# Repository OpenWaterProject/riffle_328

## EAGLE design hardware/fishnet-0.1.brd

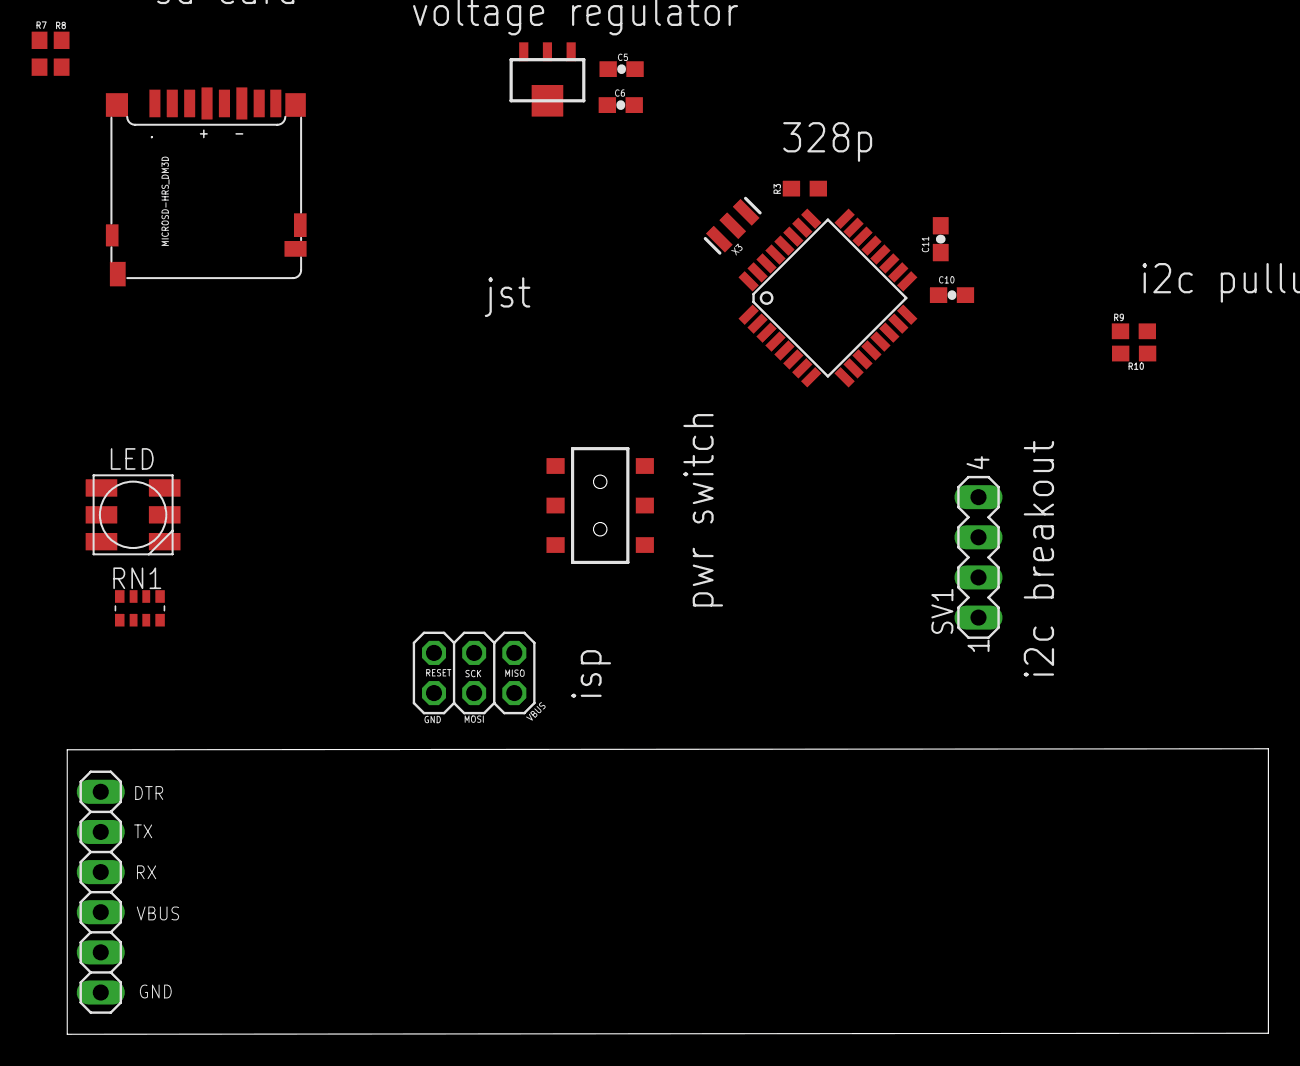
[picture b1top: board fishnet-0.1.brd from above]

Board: 2 copper layers, 76.0 x 18.1 mm, 20 parts (1 on the bottom side), 25 nets, no tracks yet.

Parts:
C5, C6: 10uF; 0603-CAP
C10, C11: 0.1uF; 0603-CAP
CN1: JST-PH-2-SMT-RA
IC1: ATMEGA328P; TQFP32-08
IC4: MCP1700-33; SOT89
ISP: 2X03
J1: AYZ0202
JP2: 1X06
LED: RGBLED5050
R3, R9, R10: 10K; 0603-NO
R7, R8: 50K; 0603-NO
RN1: EXB38V
SV1: MA04-1
U$1: MICROSD-HRS_DM3D; DM3D
X3: 16 MHz; RESONATOR-SMD

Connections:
AREF: C10.1, IC1.20
D4: IC1.2, RN1.4
D5: IC1.9, RN1.2
D6: IC1.10, RN1.3
D7: IC1.11, U$1.CD/DAT3
GND: C5.2, C6.2, C10.2, C11.1, CN1.2, IC1.3, IC1.5, IC1.21, IC4.1, ISP.6, JP2.1, LED.4, LED.5, LED.6, SV1.2, U$1.GND1, U$1.GND2, U$1.GND3, U$1.GND4, U$1.SW_A, U$1.SW_B, U$1.VSS, X3.2
MISO: IC1.16, ISP.1, U$1.DAT0
MOSI: IC1.15, ISP.4, U$1.CMD
unnamed: LED.3, RN1.5
unnamed: IC1.7, X3.1
unnamed: IC1.8, X3.3
unnamed: LED.1, RN1.7
unnamed: LED.2, RN1.6
unnamed: R7.2, U$1.DAT1
unnamed: R8.1, U$1.DAT2
RESET: IC1.29, ISP.5, R3.1
RXD: IC1.30, JP2.4
SCK: IC1.17, ISP.3, U$1.CLK
SCL: IC1.28, R9.1, SV1.3
SDA: IC1.27, R10.1, SV1.4
TXD: IC1.31, JP2.5
VBAT: CN1.1, J1.2
VBUS: ISP.2, JP2.3
VCC: C6.1, C11.2, IC1.4, IC1.6, IC1.18, IC4.3, R3.2, R7.1, R8.2, R9.2, R10.2, SV1.1, U$1.VDD
VDD: C5.1, IC4.2, J1.1

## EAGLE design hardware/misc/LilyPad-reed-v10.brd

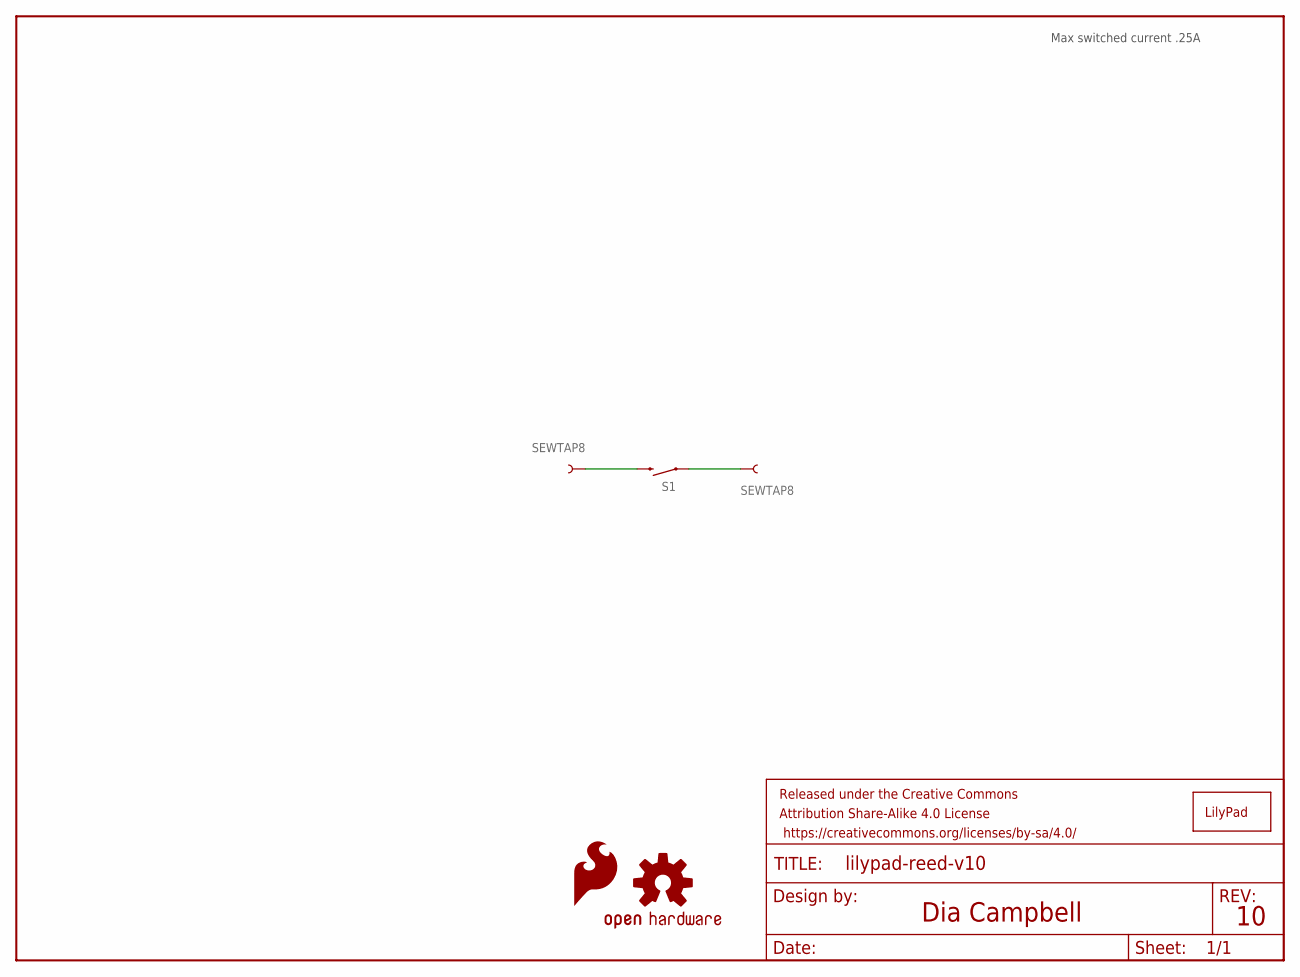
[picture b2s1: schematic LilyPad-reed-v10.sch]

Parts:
FRAME1: FRAME-LETTER; CREATIVE_COMMONS
LOGO1: OSHW-LOGOS-COPPER; OSHW-LOGO-S_COPPER
LOGO2: SFE_LOGO_FLAME.1COP; SFE_LOGO_FLAME_COPPER_.1
S1: REED; REED_SWITCH_PLASTIC
SLIDEOFF: SEWTAP8; PETAL-MEDIUM-2SIDE
SLIDEON: SEWTAP8; PETAL-MEDIUM-2SIDE
U$1: LOGO-LPLP; LOGO-LILYPAD

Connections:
unnamed: S1.P$2 (2), SLIDEOFF.1
unnamed: S1.P$1 (1), SLIDEON.1

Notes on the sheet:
Dia Campbell
Max switched current .25A

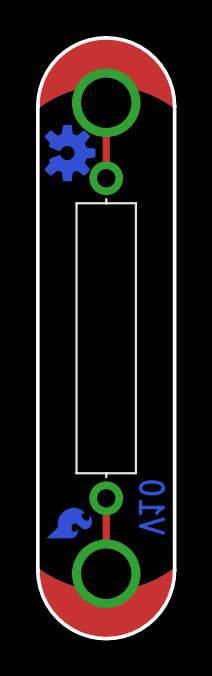
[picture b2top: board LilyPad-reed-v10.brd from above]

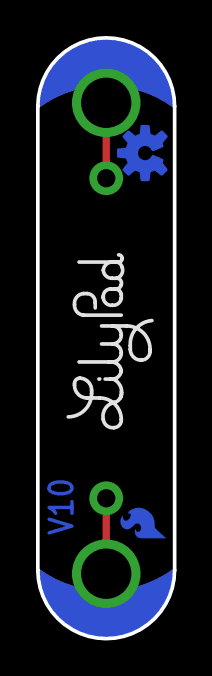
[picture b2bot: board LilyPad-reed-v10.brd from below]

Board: 2 copper layers, 7.6 x 33.4 mm, 7 parts (3 on the bottom side), 2 nets.

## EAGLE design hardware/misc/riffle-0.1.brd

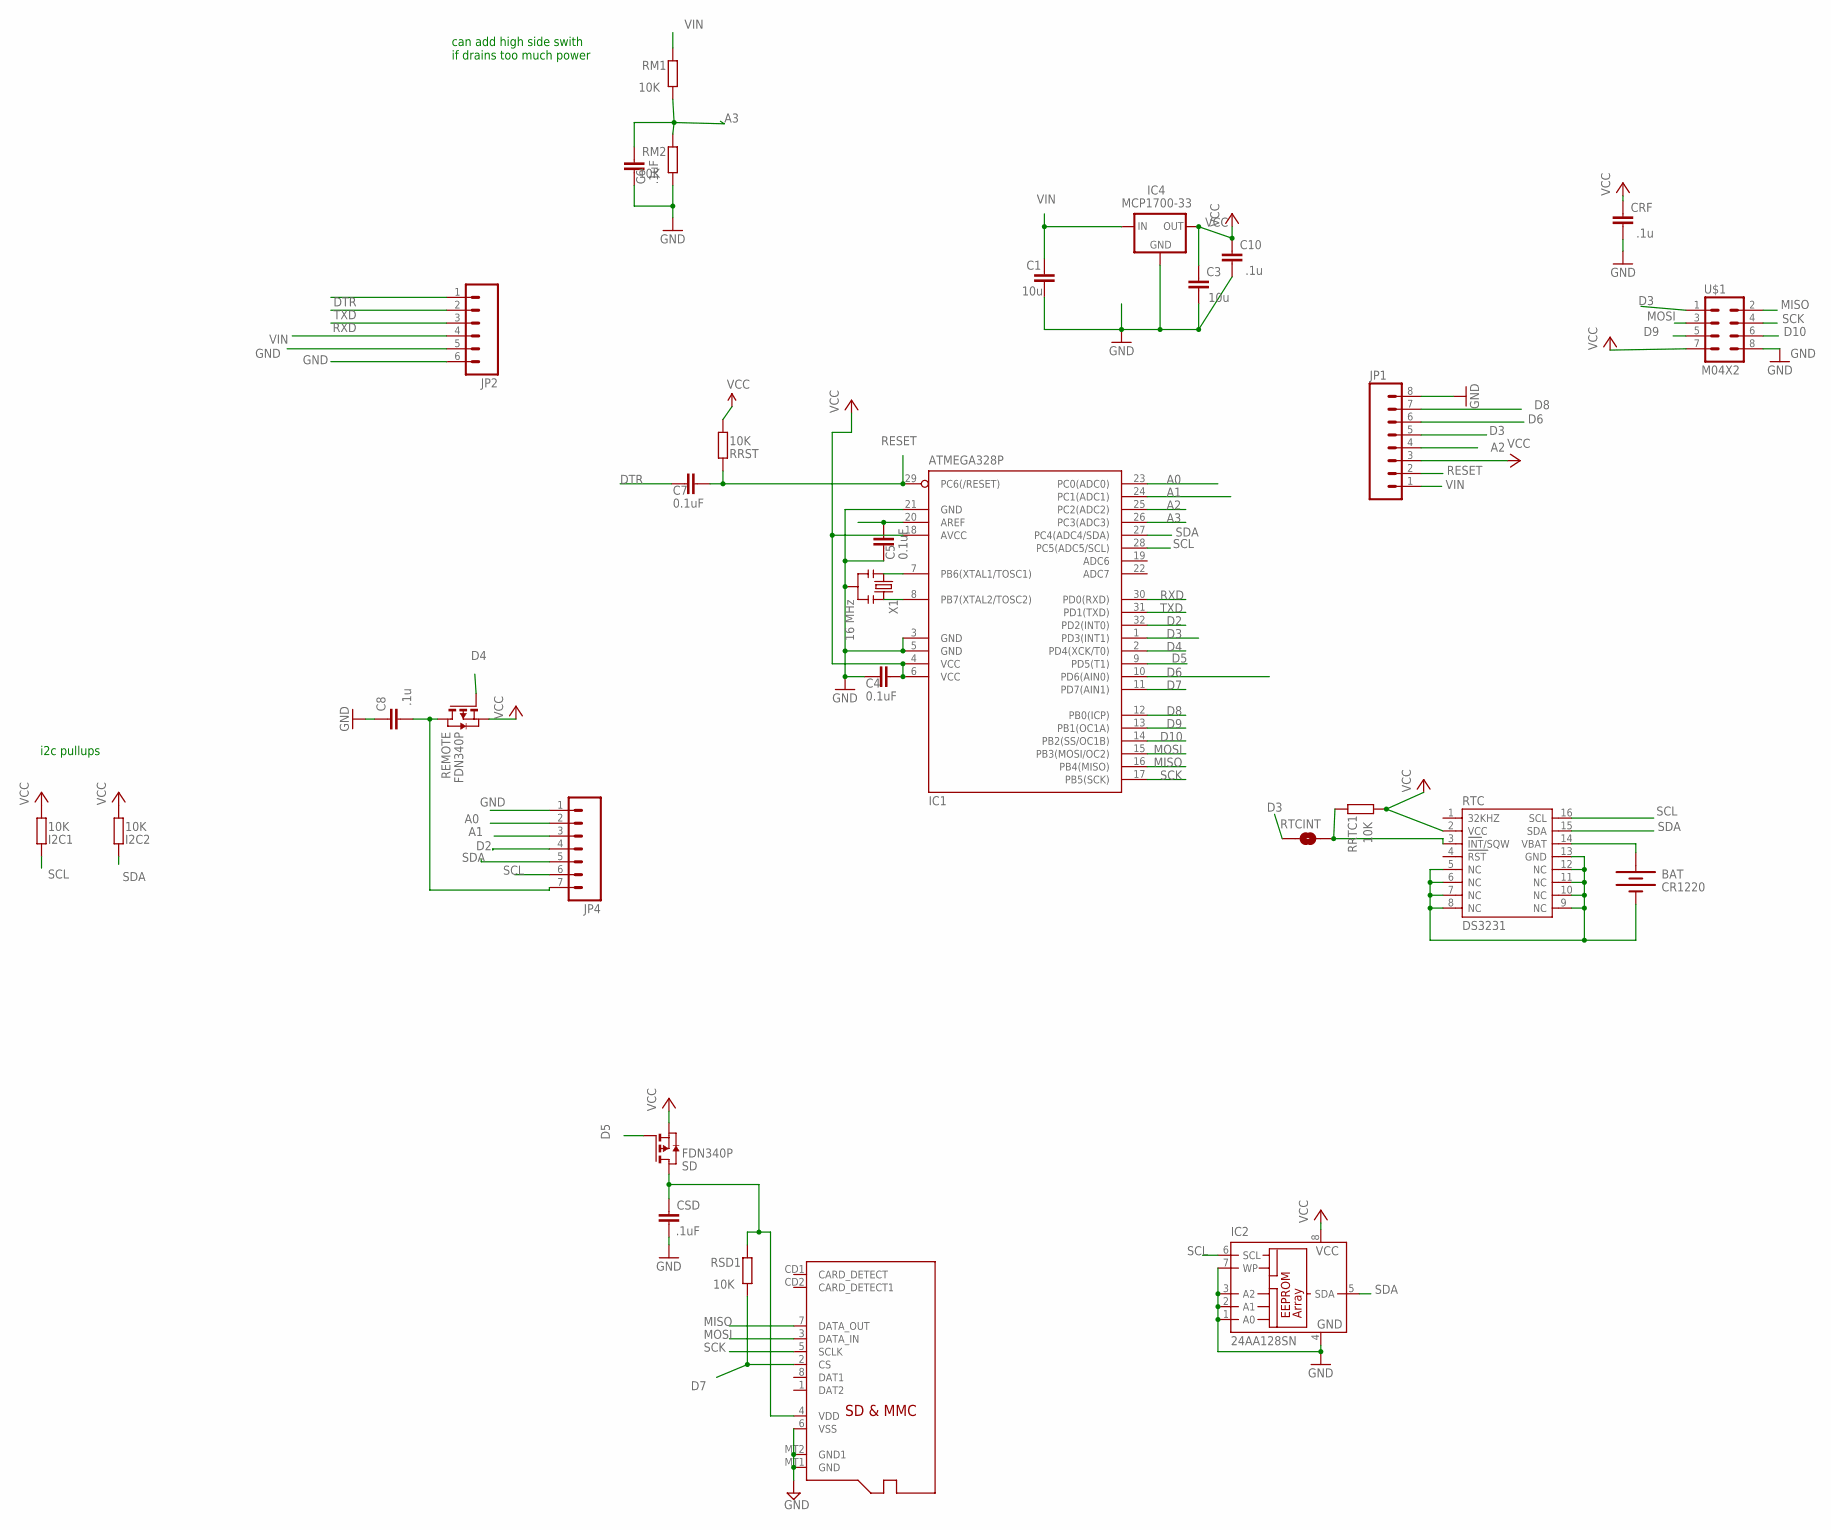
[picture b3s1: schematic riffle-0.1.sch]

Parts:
BAT: CR1220; BATTCON_12MM_SMT
C1, C3: 10u; C0805
C4, C5, C7: 0.1uF; C0805@1
C6: .1uF; C0805@1
C8, C10: .1u; C0805
CRF: .1u; C0805
CSD: .1uF; C0805
I2C1, I2C2: 10K; R0805
IC1: ATMEGA328P; TQFP32-08
IC2: 24AA128SN; SO-08
IC4: MCP1700-33; SOT23
JP1: M081X08; 1X08
JP2: M06SIP; 1X06
JP4: M07; 1X07
MICROSD: MICROSD
REMOTE: FDN340P; SOT-23
RM1, RM2: 10K; R0805
RRST: 10K; R0805
RRTC1: 10K; R0805
RSD1: 10K; R0805
RTC: DS3231
RTCINT: SOLDERJUMPERNO; SJ_2S-NO
SD: FDN340P; SOT-23
U$1: M04X2; 2X4
X1: 16 MHz; RESONATOR-SMD

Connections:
A0: IC1.23 (PC0(ADC0)), JP4.2
A1: IC1.24 (PC1(ADC1)), JP4.3
A2: IC1.25 (PC2(ADC2)), JP1.4
A3: C6.2, IC1.26 (PC3(ADC3)), RM1.1, RM2.2
AREF: C5.2, IC1.20 (AREF)
D2: IC1.32 (PD2(INT0)), JP4.4
D3: IC1.1 (PD3(INT1)), JP1.5, RTCINT.2, U$1.1
D4: IC1.2 (PD4(XCK/T0)), REMOTE.3 (G)
D5: IC1.9 (PD5(T1)), SD.3 (G)
D6: IC1.10 (PD6(AIN0)), JP1.6
D7: IC1.11 (PD7(AIN1)), MICROSD.2 (CS), RSD1.1
D8: IC1.12 (PB0(ICP)), JP1.7
D9: IC1.13 (PB1(OC1A)), U$1.5
D10: IC1.14 (PB2(SS/OC1B)), U$1.6
DTR: C7.1, JP2.1
GND: BAT.P$1 (-), C1.2, C3.2, C4.1, C5.1, C6.1, C8.1, C10.2, CRF.2, CSD.2, IC1.3 (GND), IC1.5 (GND), IC1.21 (GND), IC2.1 (A0), IC2.2 (A1), IC2.3 (A2), IC2.4 (GND), IC2.7 (WP), IC4.1 (GND), JP1.8, JP2.5, JP2.6, JP4.1, MICROSD.6 (VSS), MICROSD.MT1 (GND), MICROSD.MT2 (GND1), RM2.1, RTC.5 (NC), RTC.6 (NC), RTC.7 (NC), RTC.8 (NC), RTC.9 (NC), RTC.10 (NC), RTC.11 (NC), RTC.12 (NC), RTC.13 (GND), U$1.8, X1.2
MISO: IC1.16 (PB4(MISO)), MICROSD.7 (DATA_OUT), U$1.2
MOSI: IC1.15 (PB3(MOSI/OC2)), MICROSD.3 (DATA_IN), U$1.3
unnamed: RRTC1.2, RTC.3 (INT/SQW), RTCINT.1
unnamed: IC1.8 (PB7(XTAL2/TOSC2)), X1.3
unnamed: IC1.7 (PB6(XTAL1/TOSC1)), X1.1
unnamed: C8.2, JP4.7, REMOTE.1 (D)
RESET: C7.2, IC1.29 (PC6(/RESET)), JP1.2, RRST.2
RTC_BATT: BAT.P$2 (+), RTC.14 (VBAT)
RXD: IC1.30 (PD0(RXD)), JP2.3
SCK: IC1.17 (PB5(SCK)), MICROSD.5 (SCLK), U$1.4
SCL: I2C1.2, IC1.28 (PC5(ADC5/SCL)), IC2.6 (SCL), JP4.6, RTC.16 (SCL)
SDA: I2C2.2, IC1.27 (PC4(ADC4/SDA)), IC2.5 (SDA), JP4.5, RTC.15 (SDA)
TXD: IC1.31 (PD1(TXD)), JP2.2
VCC: C3.1, C4.2, C10.1, CRF.1, I2C1.1, I2C2.1, IC1.4 (VCC), IC1.6 (VCC), IC1.18 (AVCC), IC2.8 (VCC), IC4.2 (OUT), JP1.3, REMOTE.2 (S), RRST.1, RRTC1.1, RTC.2 (VCC), SD.2 (S), U$1.7
VDD: CSD.1, MICROSD.4 (VDD), RSD1.2, SD.1 (D)
VIN: C1.1, IC4.3 (IN), JP1.1, JP2.4, RM1.2

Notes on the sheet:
can add high side swith if drains too much power
i2c pullups

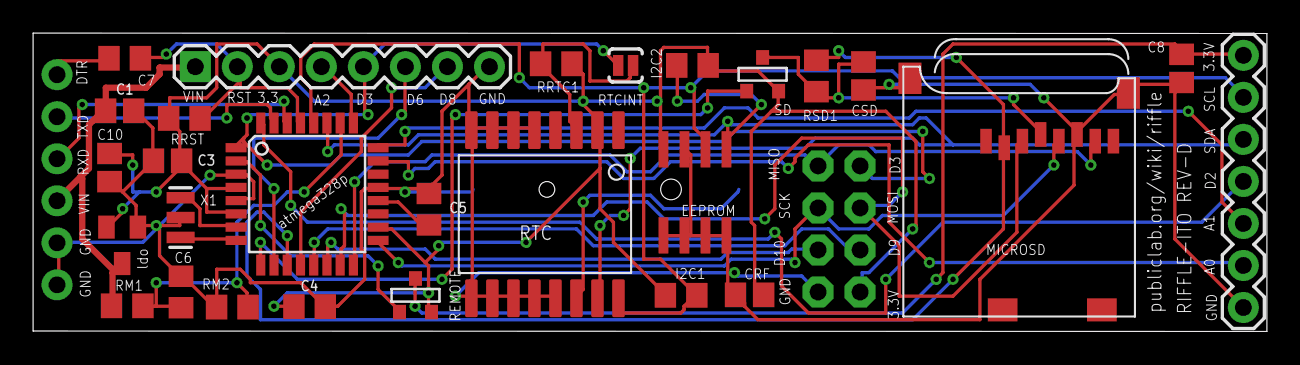
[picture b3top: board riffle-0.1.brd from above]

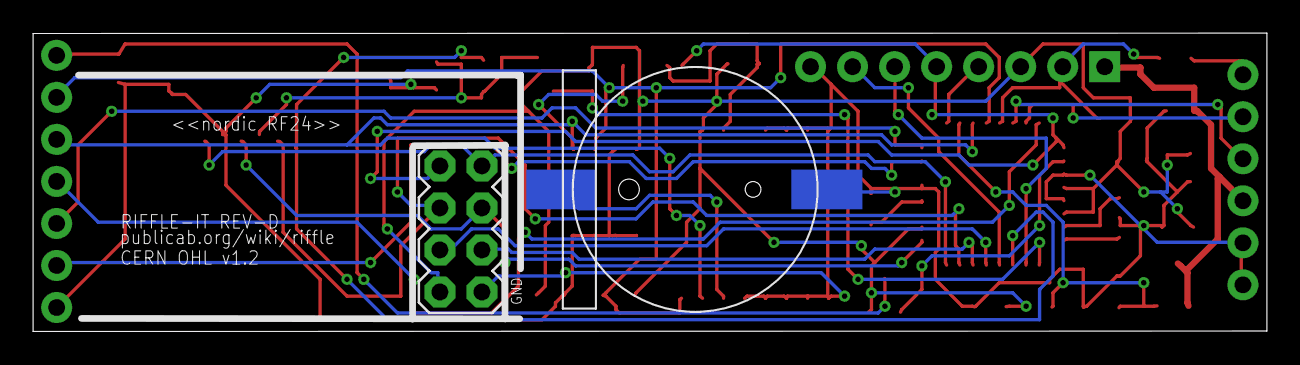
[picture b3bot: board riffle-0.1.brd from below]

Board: 2 copper layers, 74.6 x 18.0 mm, 31 parts (2 on the bottom side), 32 nets.

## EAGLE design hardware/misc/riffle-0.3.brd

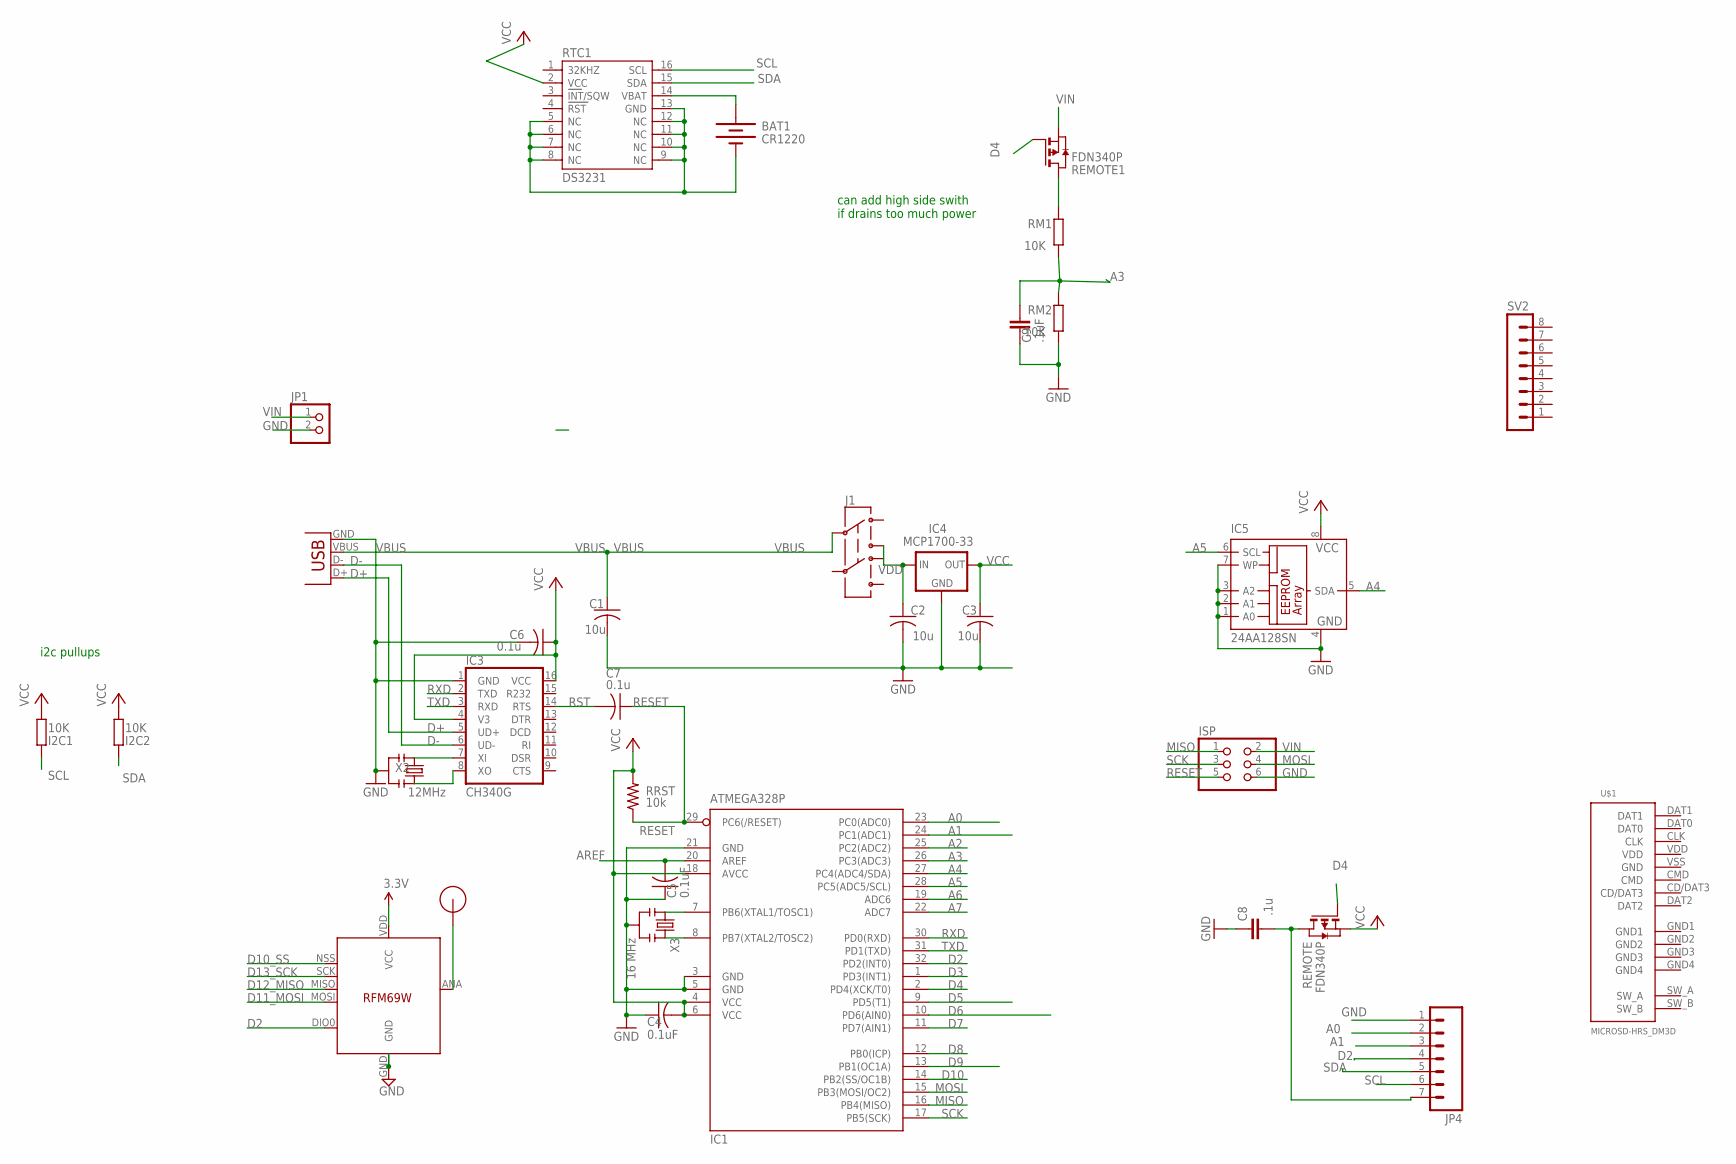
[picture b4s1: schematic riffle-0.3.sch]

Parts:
BAT1: CR1220; BATTCON_12MM_SMT
C1, C2, C3: 10u; C0805K
C4, C5: 0.1uF; C0805K
C6, C7: 0.1u; C0805K
C8: .1u; C0805
C9: .1uF; C0805@1
I2C1, I2C2: 10K; R0805
IC1: ATMEGA328P; TQFP32-08
IC3: CH340G; SO16
IC4: MCP1700-33; SOT89
IC5: 24AA128SN; SO-08
ISP: PINHD-2X3; 2X03
J1: AYZ0202
JP1: PINHD-1X2; 1X02
JP4: M07; 1X07
REMOTE, REMOTE1: FDN340P; SOT-23
RM1, RM2: 10K; R0805
RRST: 10k; R0805
RTC1: DS3231
SV2: MA08-1
U$1: MICROSD-HRS_DM3D; DM3D
U$3: RFM12B_ANTENNA; RFM12B-ANTENNA
U$5: RFM69; RFM69W-MINPADS
X1: USBSMD; USB-MINIB
X2: 12MHz; RESONATOR-SMD
X3: 16 MHz; RESONATOR-SMD

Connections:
A0: IC1.23 (PC0(ADC0)), JP4.2
A1: IC1.24 (PC1(ADC1)), JP4.3
A2: IC1.25 (PC2(ADC2))
A3: C9.2, IC1.26 (PC3(ADC3)), RM1.1, RM2.2
A4: IC1.27 (PC4(ADC4/SDA)), IC5.5 (SDA)
A5: IC1.28 (PC5(ADC5/SCL)), IC5.6 (SCL)
A6: IC1.19 (ADC6)
A7: IC1.22 (ADC7)
AREF: C5.2, IC1.20 (AREF)
D2: IC1.32 (PD2(INT0)), JP4.4, U$5.DIO0
D3: IC1.1 (PD3(INT1))
D4: IC1.2 (PD4(XCK/T0)), REMOTE.3 (G), REMOTE1.3 (G)
D5: IC1.9 (PD5(T1))
D6: IC1.10 (PD6(AIN0))
D7: IC1.11 (PD7(AIN1))
D8: IC1.12 (PB0(ICP))
D9: IC1.13 (PB1(OC1A))
D10: IC1.14 (PB2(SS/OC1B))
D10_SS: U$5.NSS (SEL)
D11_MOSI: U$5.MOSI
D12_MISO: U$5.MISO
D13_SCK: U$5.SCK
D+: IC3.5 (UD+), X1.D+
D-: IC3.6 (UD-), X1.D-
GND: BAT1.P$1 (-), C1.2, C2.2, C3.2, C4.1, C5.1, C6.2, C8.1, C9.1, IC1.3 (GND), IC1.5 (GND), IC1.21 (GND), IC3.1 (GND), IC4.1 (GND), IC5.1 (A0), IC5.2 (A1), IC5.3 (A2), IC5.4 (GND), IC5.7 (WP), ISP.6, JP1.2, JP4.1, RM2.1, RTC1.5 (NC), RTC1.6 (NC), RTC1.7 (NC), RTC1.8 (NC), RTC1.9 (NC), RTC1.10 (NC), RTC1.11 (NC), RTC1.12 (NC), RTC1.13 (GND), U$5.GND, X1.GND, X2.2, X3.2
MISO: IC1.16 (PB4(MISO)), ISP.1
MOSI: IC1.15 (PB3(MOSI/OC2)), ISP.4
unnamed: U$3.P$1, U$5.ANA (ANT)
unnamed: IC1.7 (PB6(XTAL1/TOSC1)), X3.1
unnamed: IC1.8 (PB7(XTAL2/TOSC2)), X3.3
unnamed: REMOTE1.1 (D), RM1.2
unnamed: C8.2, JP4.7, REMOTE.1 (D)
unnamed: IC3.7 (XI), X2.1
unnamed: IC3.8 (XO), X2.3
RESET: C7.1, IC1.29 (PC6(/RESET)), ISP.5, RRST.1
RST: C7.2, IC3.14 (RTS)
RTC_BATT1: BAT1.P$2 (+), RTC1.14 (VBAT)
RXD: IC1.30 (PD0(RXD)), IC3.2 (TXD)
SCK: IC1.17 (PB5(SCK)), ISP.3
SCL: I2C1.2, JP4.6, RTC1.16 (SCL)
SDA: I2C2.2, JP4.5, RTC1.15 (SDA)
TXD: IC1.31 (PD1(TXD)), IC3.3 (RXD)
VBUS: C1.1, J1.2, X1.VBUS
VCC: C3.1, C4.2, C6.1, I2C1.1, I2C2.1, IC1.4 (VCC), IC1.6 (VCC), IC1.18 (AVCC), IC3.4 (V3), IC3.16 (VCC), IC4.3 (OUT), IC5.8 (VCC), REMOTE.2 (S), RRST.2, RTC1.2 (VCC), U$5.VDD (VCC)
VDD: C2.1, IC4.2 (IN), J1.1 (3)
VIN: ISP.2, JP1.1, REMOTE1.2 (S)

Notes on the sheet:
i2c pullups
can add high side swith if drains too much power

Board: 2 copper layers, 33 parts (1 on the bottom side), 32 nets, no tracks yet.

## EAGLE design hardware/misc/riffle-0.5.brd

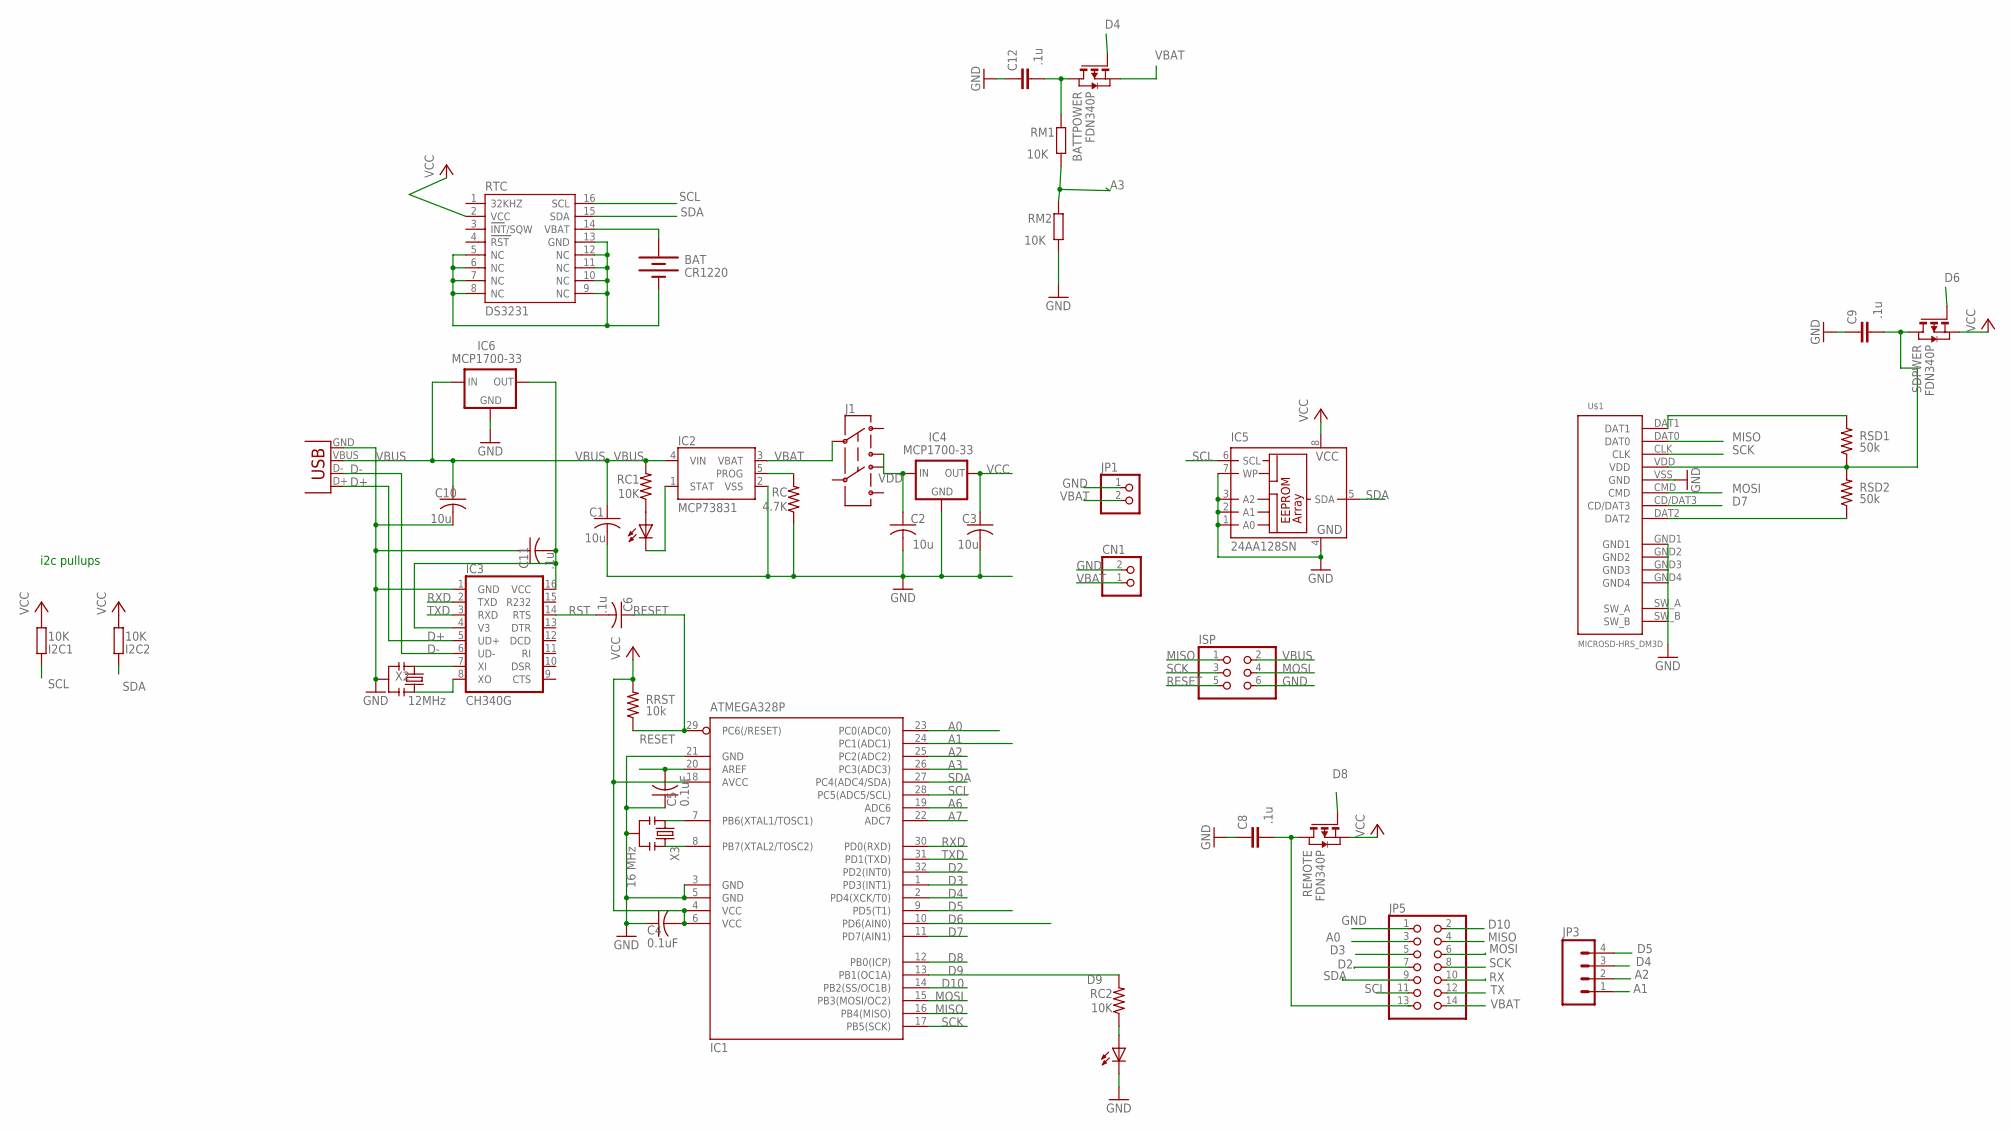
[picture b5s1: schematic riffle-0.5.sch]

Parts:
BAT: CR1220; BATTCON_12MM_SMT
BATTPOWER: FDN340P; SOT-23
C1, C2, C3, C10: 10u; C0805K
C4, C5: 0.1uF; C0805K
C6, C11: .1u; C0805K
C8, C9, C12: .1u; C0805
CHG: 0805; CHIPLED_0805
CN1: JST_2PIN-SMT-RA; JST-PH-2-SMT-RA
I2C1, I2C2: 10K; R0805
IC1: ATMEGA328P; TQFP32-08
IC2: MCP73831; SOT23-5
IC3: CH340G; SO16
IC4, IC6: MCP1700-33; SOT89
IC5: 24AA128SN; SO-08
ISP: PINHD-2X3; 2X03
J1: AYZ0202
JP1: PINHD-1X2; 1X02
JP3: M04SMD; 1X04-SMD
JP5: PINHD-2X7; 2X07
RC: 4.7K; R0805
RC1, RC2: 10K; R0805
REMOTE: FDN340P; SOT-23
RM1, RM2: 10K; R0805
RRST: 10k; R0805
RSD1, RSD2: 50k; R0805
RTC: DS3231
SDPWER: FDN340P; SOT-23
STAT: 0805; CHIPLED_0805
U$1: MICROSD-HRS_DM3D; DM3D
X1: USBSMD; USB-MINIB
X2: 12MHz; RESONATOR-SMD
X3: 16 MHz; RESONATOR-SMD

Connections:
A0: IC1.23 (PC0(ADC0)), JP5.3
A1: IC1.24 (PC1(ADC1)), JP3.1
A2: IC1.25 (PC2(ADC2)), JP3.2
A3: IC1.26 (PC3(ADC3)), RM1.1, RM2.2
A6: IC1.19 (ADC6)
A7: IC1.22 (ADC7)
AREF: C5.2, IC1.20 (AREF)
D2: IC1.32 (PD2(INT0)), JP5.7
D3: IC1.1 (PD3(INT1)), JP5.5
D4: BATTPOWER.3 (G), IC1.2 (PD4(XCK/T0)), JP3.3
D5: IC1.9 (PD5(T1)), JP3.4
D6: IC1.10 (PD6(AIN0)), SDPWER.3 (G)
D7: IC1.11 (PD7(AIN1)), U$1.CD/DAT3
D8: IC1.12 (PB0(ICP)), REMOTE.3 (G)
D9: IC1.13 (PB1(OC1A)), RC2.2
D10: IC1.14 (PB2(SS/OC1B)), JP5.2
D+: IC3.5 (UD+), X1.D+
D-: IC3.6 (UD-), X1.D-
GND: BAT.P$1 (-), C1.2, C2.2, C3.2, C4.1, C5.1, C8.1, C9.1, C10.2, C11.1, C12.1, CN1.2 (1), IC1.3 (GND), IC1.5 (GND), IC1.21 (GND), IC2.2 (VSS), IC3.1 (GND), IC4.1 (GND), IC5.1 (A0), IC5.2 (A1), IC5.3 (A2), IC5.4 (GND), IC5.7 (WP), IC6.1 (GND), ISP.6, JP1.1, JP5.1, RC.1, RM2.1, RTC.5 (NC), RTC.6 (NC), RTC.7 (NC), RTC.8 (NC), RTC.9 (NC), RTC.10 (NC), RTC.11 (NC), RTC.12 (NC), RTC.13 (GND), STAT.C, U$1.GND1, U$1.GND2, U$1.GND3, U$1.GND4, U$1.SW_A, U$1.SW_B, U$1.VSS (GND), X1.GND, X2.2, X3.2
MISO: IC1.16 (PB4(MISO)), ISP.1, JP5.4, U$1.DAT0
MOSI: IC1.15 (PB3(MOSI/OC2)), ISP.4, JP5.6, U$1.CMD
unnamed: IC1.7 (PB6(XTAL1/TOSC1)), X3.1
unnamed: IC1.8 (PB7(XTAL2/TOSC2)), X3.3
unnamed: C9.2, RSD1.1, RSD2.2, SDPWER.1 (D), U$1.VDD
unnamed: CHG.C, IC2.1 (STAT)
unnamed: IC2.5 (PROG), RC.2
unnamed: C8.2, JP5.13, REMOTE.1 (D)
unnamed: C11.2, IC3.4 (V3), IC3.16 (VCC), IC6.3 (OUT)
unnamed: CHG.A, RC1.1
unnamed: IC3.7 (XI), X2.1
unnamed: IC3.8 (XO), X2.3
unnamed: BATTPOWER.1 (D), C12.2, RM1.2
unnamed: RSD1.2, U$1.DAT1
unnamed: RC2.1, STAT.A
unnamed: RSD2.1, U$1.DAT2
RESET: C6.1, IC1.29 (PC6(/RESET)), ISP.5, RRST.1
RST: C6.2, IC3.14 (RTS)
RTC_BATT: BAT.P$2 (+), RTC.14 (VBAT)
RX: JP5.10
RXD: IC1.30 (PD0(RXD)), IC3.2 (TXD)
SCK: IC1.17 (PB5(SCK)), ISP.3, JP5.8, U$1.CLK
SCL: I2C1.2, IC1.28 (PC5(ADC5/SCL)), IC5.6 (SCL), JP5.11, RTC.16 (SCL)
SDA: I2C2.2, IC1.27 (PC4(ADC4/SDA)), IC5.5 (SDA), JP5.9, RTC.15 (SDA)
TX: JP5.12
TXD: IC1.31 (PD1(TXD)), IC3.3 (RXD)
VBAT: BATTPOWER.2 (S), CN1.1 (2), IC2.3 (VBAT), J1.2, JP1.2, JP5.14
VBUS: C1.1, C10.1, IC2.4 (VIN), IC6.2 (IN), ISP.2, RC1.2, X1.VBUS
VCC: C3.1, C4.2, I2C1.1, I2C2.1, IC1.4 (VCC), IC1.6 (VCC), IC1.18 (AVCC), IC4.3 (OUT), IC5.8 (VCC), REMOTE.2 (S), RRST.2, RTC.2 (VCC), SDPWER.2 (S)
VDD: C2.1, IC4.2 (IN), J1.1 (3)

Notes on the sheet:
i2c pullups

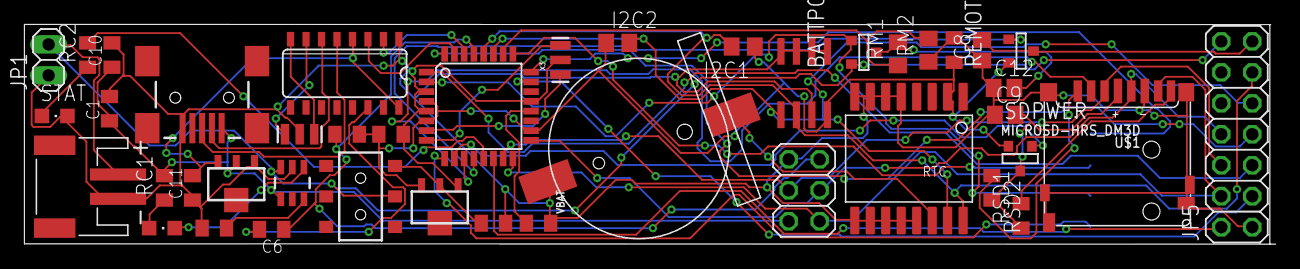
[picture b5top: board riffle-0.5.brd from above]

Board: 2 copper layers, 102.7 x 18.0 mm, 44 parts (1 on the bottom side), 45 nets.

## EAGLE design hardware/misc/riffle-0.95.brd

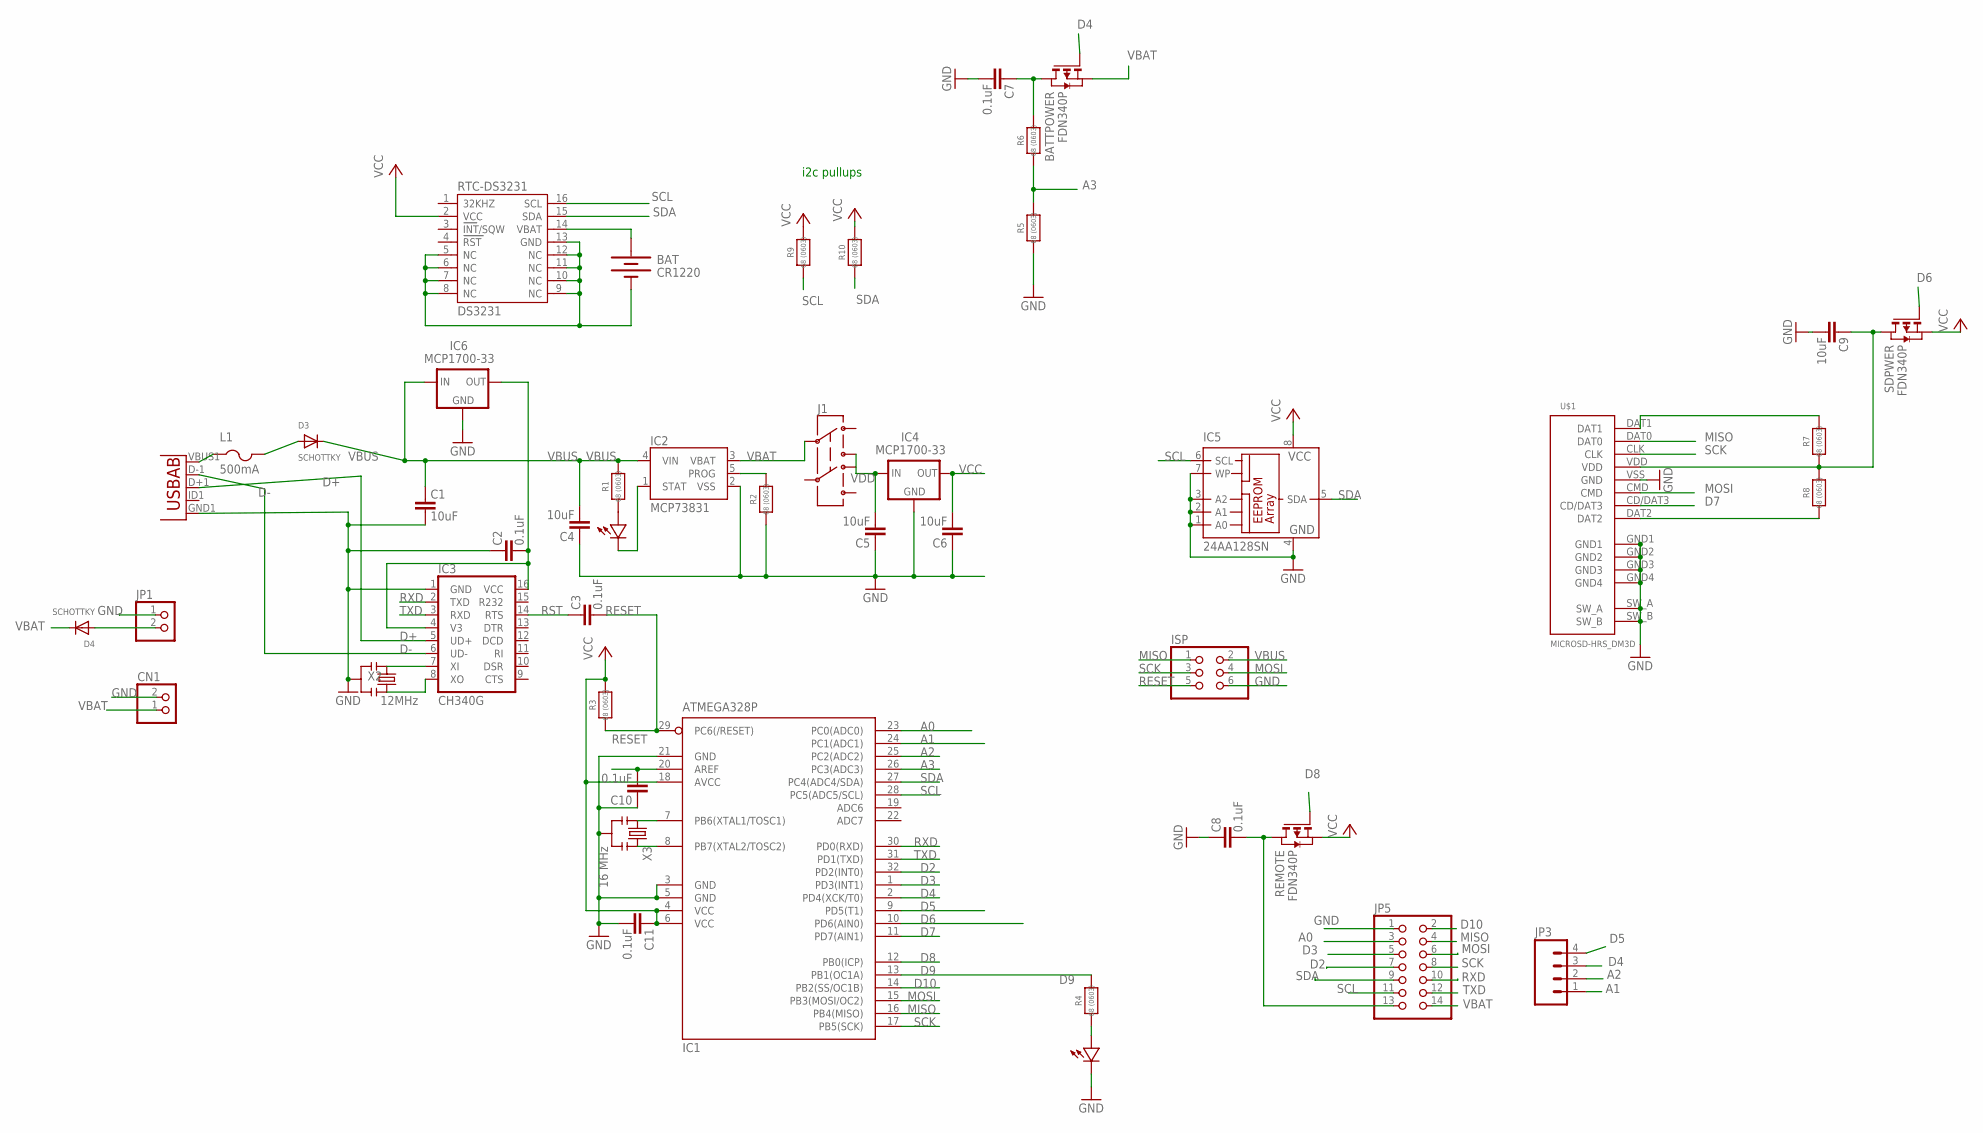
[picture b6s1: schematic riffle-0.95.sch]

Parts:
BAT: CR1220; BATTCON_12MM_SMT
BATTPOWER: FDN340P; SOT-23
C1, C4, C5, C6, C9: 10uF; 0603-CAP
C2, C3, C7, C8, C10, C11: 0.1uF; 0603-CAP
CN1: JST_2PIN-SMT-RA; JST-PH-2-SMT-RA
D1, D2: LED0603; 0603-LED
D3, D4: SCHOTTKY; SOD-123FL
IC1: ATMEGA328P; TQFP32-08
IC2: MCP73831; SOT23-5
IC3: CH340G; SO16
IC4, IC6: MCP1700-33; SOT89
IC5: 24AA128SN; SO-08
ISP: PINHD-2X3; 2X03
J1: AYZ0202
JP1: PINHD-1X2; 1X02
JP3: M04SMD; 1X04-SMD
JP5: PINHD-2X7; 2X07
L1: 500mA; R1206
R1, R2, R3, R4, R5, R6, R7, R8, R9, R10: 68 (0603); 0603-NO
REMOTE: FDN340P; SOT-23
RTC-DS3231: DS3231
SDPWER: FDN340P; SOT-23
U$1: MICROSD-HRS_DM3D; DM3D
U$4: USB-AB""; USB-AB-MICRO-SMD_V02_BOSS
X2: 12MHz; RESONATOR-SMD
X3: 16 MHz; RESONATOR-SMD

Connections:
A0: IC1.23 (PC0(ADC0)), JP5.3
A1: IC1.24 (PC1(ADC1)), JP3.1
A2: IC1.25 (PC2(ADC2)), JP3.2
A3: IC1.26 (PC3(ADC3)), R5.2, R6.1
AREF: C10.1, IC1.20 (AREF)
D2: IC1.32 (PD2(INT0)), JP5.7
D3: IC1.1 (PD3(INT1)), JP5.5
D4: BATTPOWER.3 (G), IC1.2 (PD4(XCK/T0)), JP3.3
D5: IC1.9 (PD5(T1)), JP3.4
D6: IC1.10 (PD6(AIN0)), SDPWER.3 (G)
D7: IC1.11 (PD7(AIN1)), U$1.CD/DAT3
D8: IC1.12 (PB0(ICP)), REMOTE.3 (G)
D9: IC1.13 (PB1(OC1A)), R4.2
D10: IC1.14 (PB2(SS/OC1B)), JP5.2
D+: IC3.5 (UD+), U$4.D+1 (D+)
D-: IC3.6 (UD-), U$4.D-1 (D-)
GND: BAT.P$1 (-), C1.1, C2.2, C4.2, C5.2, C6.2, C7.1, C8.2, C9.1, C10.2, C11.1, CN1.2 (1), D2.MINUS, IC1.3 (GND), IC1.5 (GND), IC1.21 (GND), IC2.2 (VSS), IC3.1 (GND), IC4.1 (GND), IC5.1 (A0), IC5.2 (A1), IC5.3 (A2), IC5.4 (GND), IC5.7 (WP), IC6.1 (GND), ISP.6, JP1.1, JP5.1, R2.1, R5.1, RTC-DS3231.5 (NC), RTC-DS3231.6 (NC), RTC-DS3231.7 (NC), RTC-DS3231.8 (NC), RTC-DS3231.9 (NC), RTC-DS3231.10 (NC), RTC-DS3231.11 (NC), RTC-DS3231.12 (NC), RTC-DS3231.13 (GND), U$1.GND1, U$1.GND2, U$1.GND3, U$1.GND4, U$1.SW_A, U$1.SW_B, U$1.VSS (GND), U$4.GND1 (GND), X2.2, X3.2
MISO: IC1.16 (PB4(MISO)), ISP.1, JP5.4, U$1.DAT0
MOSI: IC1.15 (PB3(MOSI/OC2)), ISP.4, JP5.6, U$1.CMD
unnamed: D1.PLUS, R1.1
unnamed: IC1.7 (PB6(XTAL1/TOSC1)), X3.1
unnamed: IC1.8 (PB7(XTAL2/TOSC2)), X3.3
unnamed: C9.2, R7.1, R8.2, SDPWER.1 (D), U$1.VDD
unnamed: D1.MINUS, IC2.1 (STAT)
unnamed: IC2.5 (PROG), R2.2
unnamed: C8.1, JP5.13, REMOTE.1 (D)
unnamed: C2.1, IC3.4 (V3), IC3.16 (VCC), IC6.3 (OUT)
unnamed: D3.A, L1.2
unnamed: IC3.7 (XI), X2.1
unnamed: IC3.8 (XO), X2.3
unnamed: D4.A, JP1.2
unnamed: BATTPOWER.1 (D), C7.2, R6.2
unnamed: R7.2, U$1.DAT1
unnamed: D2.PLUS, R4.1
unnamed: R8.1, U$1.DAT2
unnamed: L1.1, U$4.VBUS1 (VBUS)
RESET: C3.1, IC1.29 (PC6(/RESET)), ISP.5, R3.1
RST: C3.2, IC3.14 (RTS)
RTC_BATT: BAT.P$2 (+), RTC-DS3231.14 (VBAT)
RXD: IC1.30 (PD0(RXD)), IC3.2 (TXD), JP5.10
SCK: IC1.17 (PB5(SCK)), ISP.3, JP5.8, U$1.CLK
SCL: IC1.28 (PC5(ADC5/SCL)), IC5.6 (SCL), JP5.11, R9.1, RTC-DS3231.16 (SCL)
SDA: IC1.27 (PC4(ADC4/SDA)), IC5.5 (SDA), JP5.9, R10.1, RTC-DS3231.15 (SDA)
TXD: IC1.31 (PD1(TXD)), IC3.3 (RXD), JP5.12
VBAT: BATTPOWER.2 (S), CN1.1 (2), D4.C, IC2.3 (VBAT), J1.2, JP5.14
VBUS: C1.2, C4.1, D3.C, IC2.4 (VIN), IC6.2 (IN), ISP.2, R1.2
VCC: C6.1, C11.2, IC1.4 (VCC), IC1.6 (VCC), IC1.18 (AVCC), IC4.3 (OUT), IC5.8 (VCC), R3.2, R9.2, R10.2, REMOTE.2 (S), RTC-DS3231.2 (VCC), SDPWER.2 (S)
VDD: C5.1, IC4.2 (IN), J1.1 (3)

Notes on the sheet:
i2c pullups

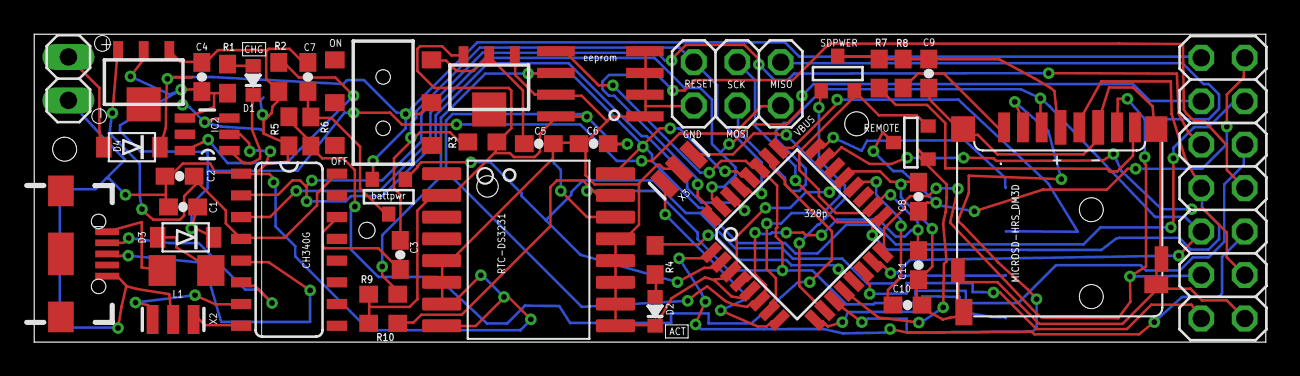
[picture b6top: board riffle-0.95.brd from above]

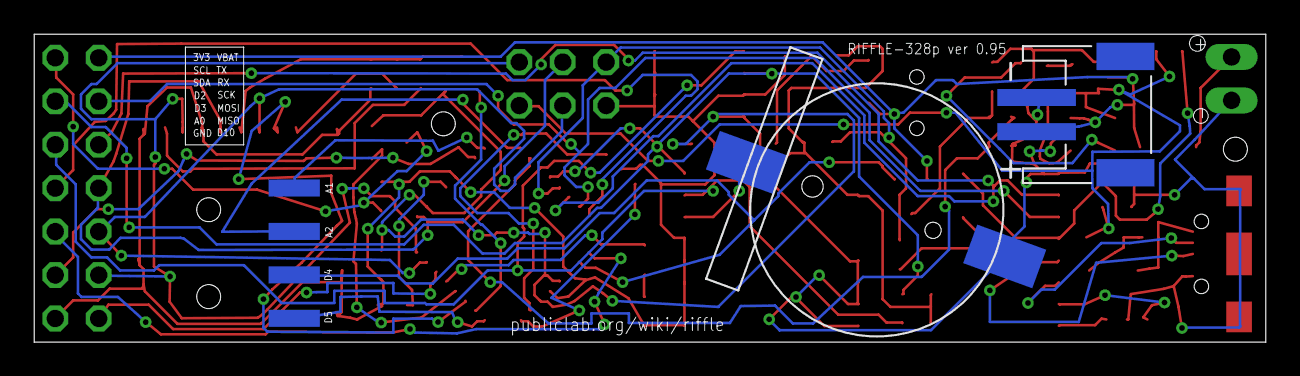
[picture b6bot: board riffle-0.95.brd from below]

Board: 2 copper layers, 72.0 x 18.0 mm, 47 parts (3 on the bottom side), 48 nets.

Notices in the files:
hardware/misc/riffle-0.1.brd:
CERN OHL v1.2
parts and their libraries:
microbuilder: This work is placed in the public domain, and may be freely used for commercial and non-commercial work with the following conditions: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
SparkFun-Electromechanical: Licensing: Creative Commons ShareAlike 4.0 International - https://creativecommons.org/licenses/by-sa/4.0
